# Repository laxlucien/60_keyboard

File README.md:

# 60_keyboard
 60% Keyboard implimentation

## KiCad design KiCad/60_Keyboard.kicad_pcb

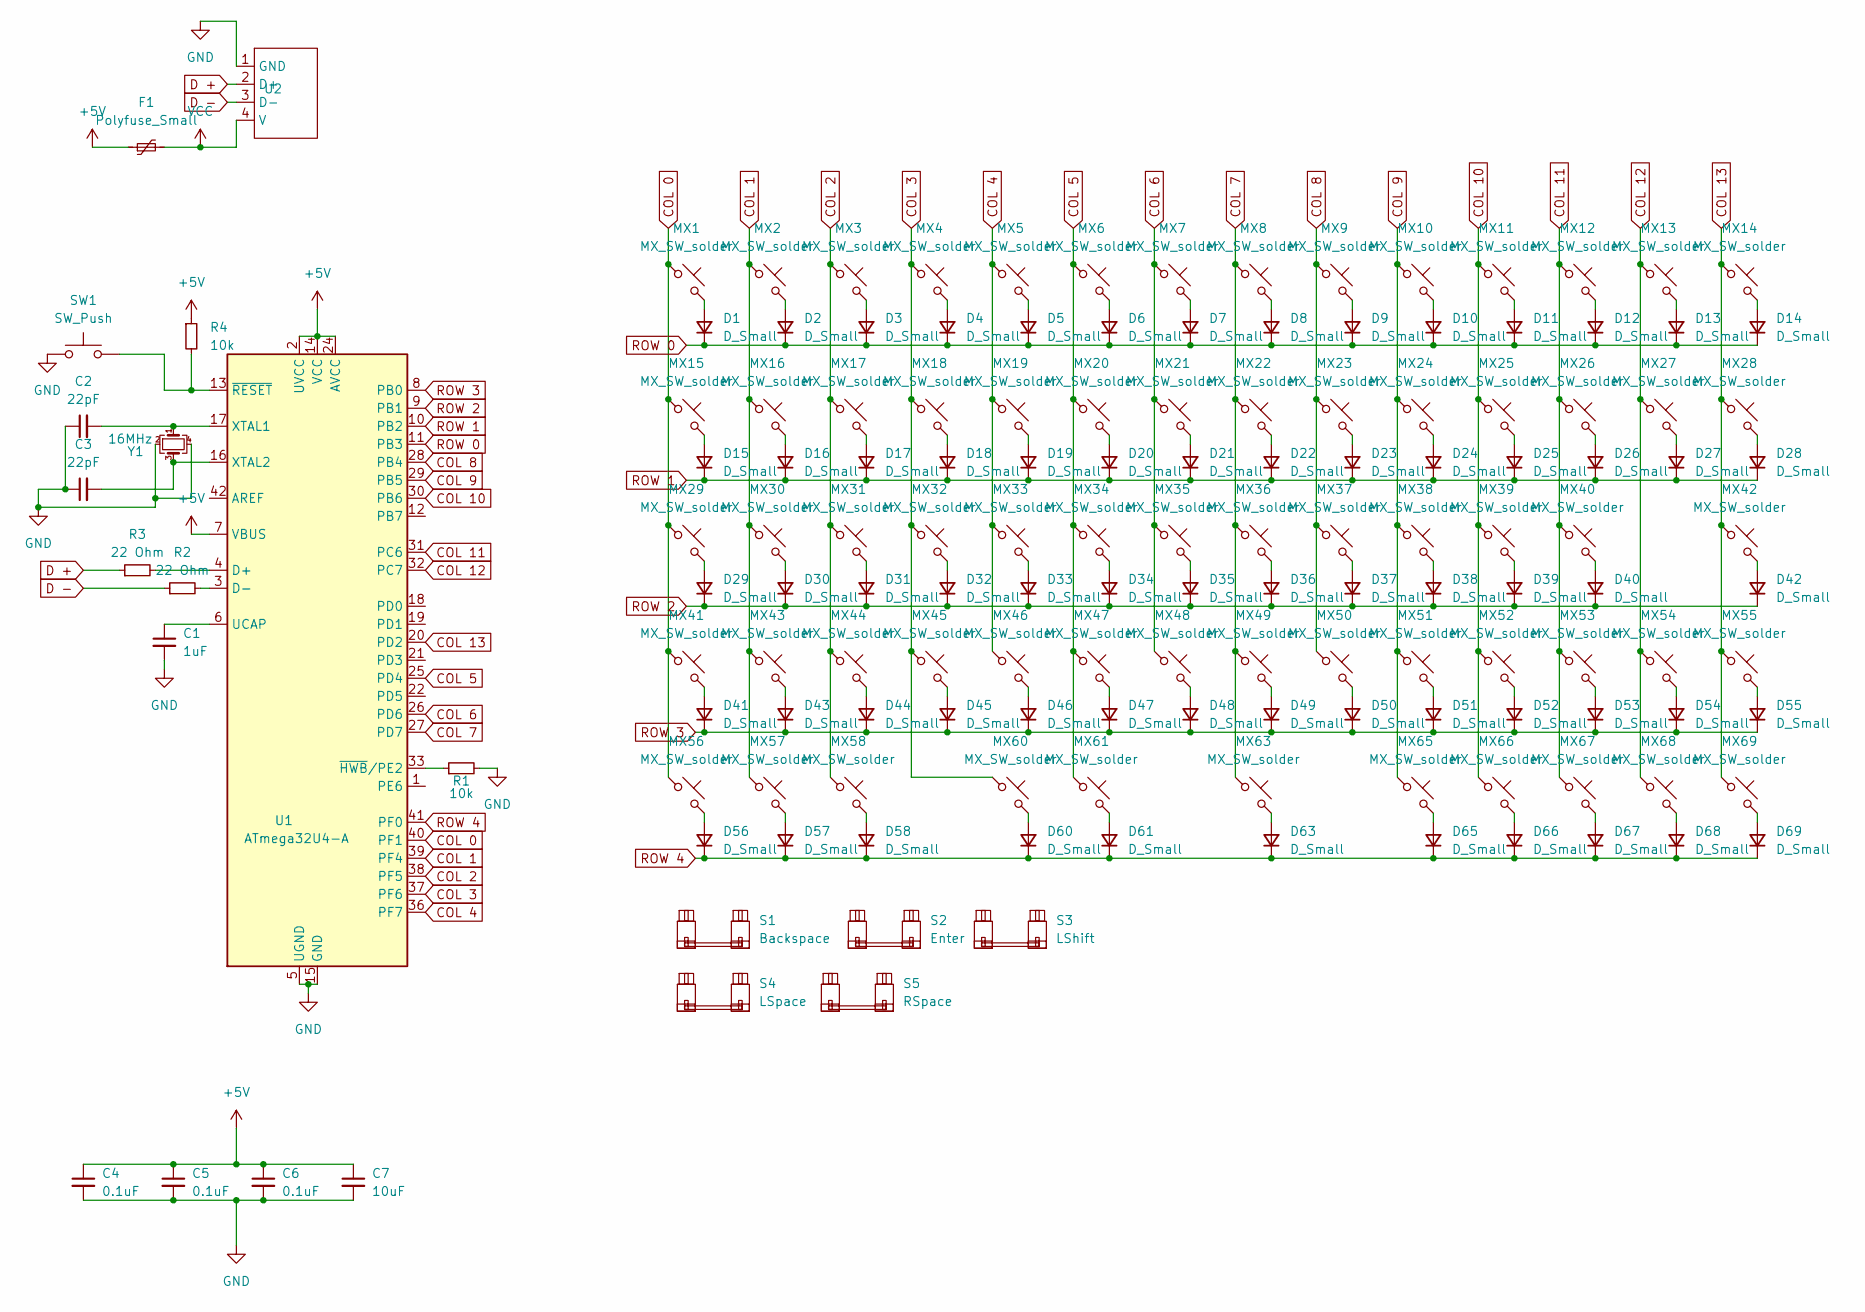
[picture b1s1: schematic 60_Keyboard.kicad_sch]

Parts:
C1: 1uF; C_0805_2012Metric
C2, C3: 22pF; C_0805_2012Metric
C4, C5, C6: 0.1uF; C_0805_2012Metric
C7: 10uF; C_0805_2012Metric
D1, D2, D3, D4, D5, D6, D7, D8, D9, D10, D11, D12, D13, D14, D15, D16, D17, D18, D19, D20, D21, D22, D23, D24, D25, D26, D27, D28, D29, D30, D31, D32, D33, D34, D35, D36, D37, D38, D39, D40, D41, D42, D43, D44, D45, D46, D47, D48, D49, D50, D51, D52, D53, D54, D55, D56, D57, D58, D60, D61, D63, D65, D66, D67, D68, D69: D_Small; D_SOD-123
F1: Polyfuse_Small; Fuse_1206_3216Metric
MX1, MX2, MX3, MX4, MX5, MX6, MX7, MX8, MX9, MX10, MX11, MX12, MX13, MX14, MX16, MX17, MX18, MX19, MX20, MX21, MX22, MX23, MX24, MX25, MX26, MX27, MX30, MX31, MX32, MX33, MX34, MX35, MX36, MX37, MX38, MX39, MX40, MX41, MX42, MX43, MX44, MX45, MX46, MX47, MX48, MX49, MX50, MX51, MX52, MX53, MX54, MX55, MX60, MX61, MX63, MX65, MX66, MX67, MX68, MX69: MX_SW_solder; SW_MX_1u
MX15, MX28: MX_SW_solder; SW_MX_1.5u
MX29: MX_SW_solder; SW_MX_1.75u
MX56, MX57, MX58: MX_SW_solder; SW_MX_1.25u
R1, R4: 10k; R_0805_2012Metric
R2, R3: 22 Ohm; R_0805_2012Metric
S1: Backspace; STAB_MX_2u
S2: Enter; STAB_MX_2.25u
S3: LShift; STAB_MX_2u
S4: LSpace; STAB_MX_2.25u
S5: RSpace; STAB_MX_3u
SW1: SW_Push; SKQG-1155865
U1: ATmega32U4-A; TQFP-44_10x10mm_P0.8mm
U2: USB-C
Y1: 16MHz; Crystal_SMD_3225-4Pin_3.2x2.5mm

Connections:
+5V: C4.1, C5.1, C6.1, C7.1, F1.1, R4.1, U1.2 (UVCC), U1.7 (VBUS), U1.14 (VCC), U1.24 (AVCC), U1.34 (VCC), U1.44 (AVCC)
COL 0: MX1.1, MX15.1, MX29.1, MX41.1, MX56.1, U1.40 (PF1)
COL 1: MX2.1, MX16.1, MX30.1, MX43.1, MX57.1, U1.39 (PF4)
COL 2: MX3.1, MX17.1, MX31.1, MX44.1, MX58.1, U1.38 (PF5)
COL 3: MX4.1, MX18.1, MX32.1, MX45.1, MX60.1, U1.37 (PF6)
COL 4: MX5.1, MX19.1, MX33.1, MX46.1, U1.36 (PF7)
COL 5: MX6.1, MX20.1, MX34.1, MX47.1, MX61.1, U1.25 (PD4)
COL 6: MX7.1, MX21.1, MX35.1, MX48.1, U1.26 (PD6)
COL 7: MX8.1, MX22.1, MX36.1, MX49.1, MX63.1, U1.27 (PD7)
COL 8: MX9.1, MX23.1, MX37.1, MX50.1, U1.28 (PB4)
COL 9: MX10.1, MX24.1, MX38.1, MX51.1, MX65.1, U1.29 (PB5)
COL 10: MX11.1, MX25.1, MX39.1, MX52.1, MX66.1, U1.30 (PB6)
COL 11: MX12.1, MX26.1, MX40.1, MX53.1, MX67.1, U1.31 (PC6)
COL 12: MX13.1, MX27.1, MX54.1, MX68.1, U1.32 (PC7)
COL 13: MX14.1, MX28.1, MX42.1, MX55.1, MX69.1, U1.20 (PD2)
D +: R3.1, U2.2 (D+)
D -: R2.1, U2.3 (D-)
GND: C1.2, C2.1, C3.1, C4.2, C5.2, C6.2, C7.2, R1.2, SW1.1, U1.5 (UGND), U1.15 (GND), U1.23 (GND), U1.35 (GND), U1.43 (GND), U2.1 (GND), Y1.2, Y1.4
unnamed: D1.2 (A), MX1.2
unnamed: D2.2 (A), MX2.2
unnamed: D3.2 (A), MX3.2
unnamed: D4.2 (A), MX4.2
unnamed: D5.2 (A), MX5.2
unnamed: D6.2 (A), MX6.2
unnamed: D7.2 (A), MX7.2
unnamed: D8.2 (A), MX8.2
unnamed: D9.2 (A), MX9.2
unnamed: D10.2 (A), MX10.2
unnamed: D11.2 (A), MX11.2
unnamed: D12.2 (A), MX12.2
unnamed: D13.2 (A), MX13.2
unnamed: D14.2 (A), MX14.2
unnamed: D15.2 (A), MX15.2
unnamed: D16.2 (A), MX16.2
unnamed: D17.2 (A), MX17.2
unnamed: D18.2 (A), MX18.2
unnamed: D19.2 (A), MX19.2
unnamed: D20.2 (A), MX20.2
unnamed: D21.2 (A), MX21.2
unnamed: D22.2 (A), MX22.2
unnamed: D23.2 (A), MX23.2
unnamed: D24.2 (A), MX24.2
unnamed: D25.2 (A), MX25.2
unnamed: D26.2 (A), MX26.2
unnamed: D27.2 (A), MX27.2
unnamed: D28.2 (A), MX28.2
unnamed: D29.2 (A), MX29.2
unnamed: D30.2 (A), MX30.2
unnamed: D31.2 (A), MX31.2
unnamed: D32.2 (A), MX32.2
unnamed: D33.2 (A), MX33.2
unnamed: D34.2 (A), MX34.2
unnamed: D35.2 (A), MX35.2
unnamed: D36.2 (A), MX36.2
unnamed: D37.2 (A), MX37.2
unnamed: D38.2 (A), MX38.2
unnamed: D39.2 (A), MX39.2
unnamed: D40.2 (A), MX40.2
unnamed: D41.2 (A), MX41.2
unnamed: D42.2 (A), MX42.2
unnamed: D43.2 (A), MX43.2
unnamed: D44.2 (A), MX44.2
unnamed: D45.2 (A), MX45.2
unnamed: D46.2 (A), MX46.2
unnamed: D47.2 (A), MX47.2
unnamed: D48.2 (A), MX48.2
unnamed: D49.2 (A), MX49.2
unnamed: D50.2 (A), MX50.2
unnamed: D51.2 (A), MX51.2
unnamed: D52.2 (A), MX52.2
unnamed: D53.2 (A), MX53.2
unnamed: D54.2 (A), MX54.2
unnamed: D55.2 (A), MX55.2
unnamed: D56.2 (A), MX56.2
unnamed: D57.2 (A), MX57.2
unnamed: D58.2 (A), MX58.2
unnamed: D60.2 (A), MX60.2
unnamed: D61.2 (A), MX61.2
unnamed: D63.2 (A), MX63.2
unnamed: D65.2 (A), MX65.2
unnamed: D66.2 (A), MX66.2
unnamed: D67.2 (A), MX67.2
unnamed: D68.2 (A), MX68.2
unnamed: D69.2 (A), MX69.2
unnamed: R3.2, U1.4 (D+)
unnamed: R2.2, U1.3 (D-)
unnamed: C1.1, U1.6 (UCAP)
unnamed: C2.2, U1.17 (XTAL1), Y1.1
unnamed: C3.2, U1.16 (XTAL2), Y1.3
unnamed: R1.1, U1.33 (~HWB/PE2)
unnamed: R4.2, SW1.2, U1.13 (~RESET)
ROW 0: D1.1 (K), D2.1 (K), D3.1 (K), D4.1 (K), D5.1 (K), D6.1 (K), D7.1 (K), D8.1 (K), D9.1 (K), D10.1 (K), D11.1 (K), D12.1 (K), D13.1 (K), D14.1 (K), U1.11 (PB3)
ROW 1: D15.1 (K), D16.1 (K), D17.1 (K), D18.1 (K), D19.1 (K), D20.1 (K), D21.1 (K), D22.1 (K), D23.1 (K), D24.1 (K), D25.1 (K), D26.1 (K), D27.1 (K), D28.1 (K), U1.10 (PB2)
ROW 2: D29.1 (K), D30.1 (K), D31.1 (K), D32.1 (K), D33.1 (K), D34.1 (K), D35.1 (K), D36.1 (K), D37.1 (K), D38.1 (K), D39.1 (K), D40.1 (K), D42.1 (K), U1.9 (PB1)
ROW 3: D41.1 (K), D43.1 (K), D44.1 (K), D45.1 (K), D46.1 (K), D47.1 (K), D48.1 (K), D49.1 (K), D50.1 (K), D51.1 (K), D52.1 (K), D53.1 (K), D54.1 (K), D55.1 (K), U1.8 (PB0)
ROW 4: D56.1 (K), D57.1 (K), D58.1 (K), D60.1 (K), D61.1 (K), D63.1 (K), D65.1 (K), D66.1 (K), D67.1 (K), D68.1 (K), D69.1 (K), U1.41 (PF0)
VCC: F1.2, U2.4 (V)

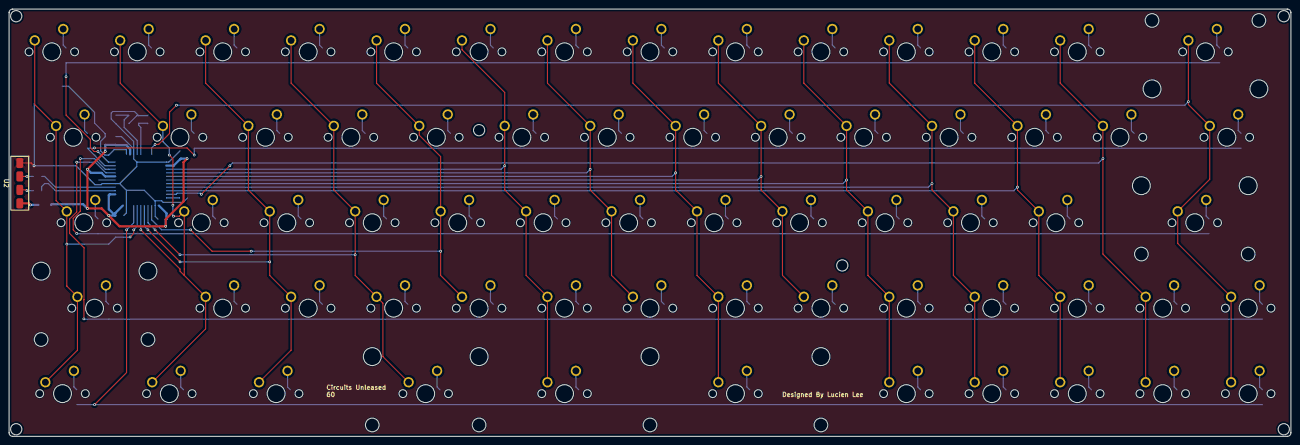
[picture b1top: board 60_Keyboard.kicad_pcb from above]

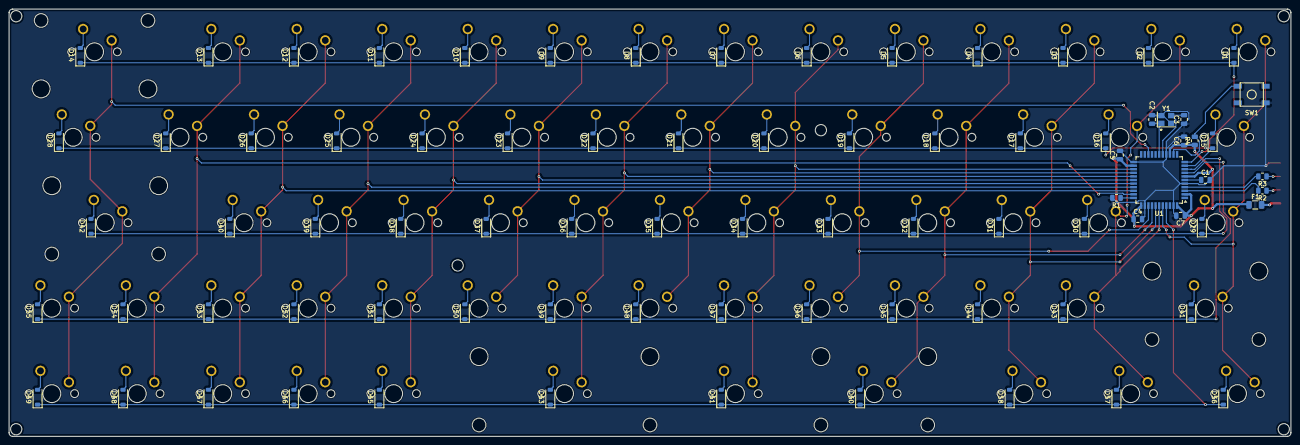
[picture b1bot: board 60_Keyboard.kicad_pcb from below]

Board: 2 copper layers, 285.7 x 95.2 mm, 153 parts (81 on the bottom side), 97 nets.

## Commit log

2024-05-19 Completed schematic and pcb
2024-05-20 Made the keyboard Back
2024-05-29 changes to gerber files and uploads of stl files that will be used
2024-06-14 Final Push, Keyboard Complete
